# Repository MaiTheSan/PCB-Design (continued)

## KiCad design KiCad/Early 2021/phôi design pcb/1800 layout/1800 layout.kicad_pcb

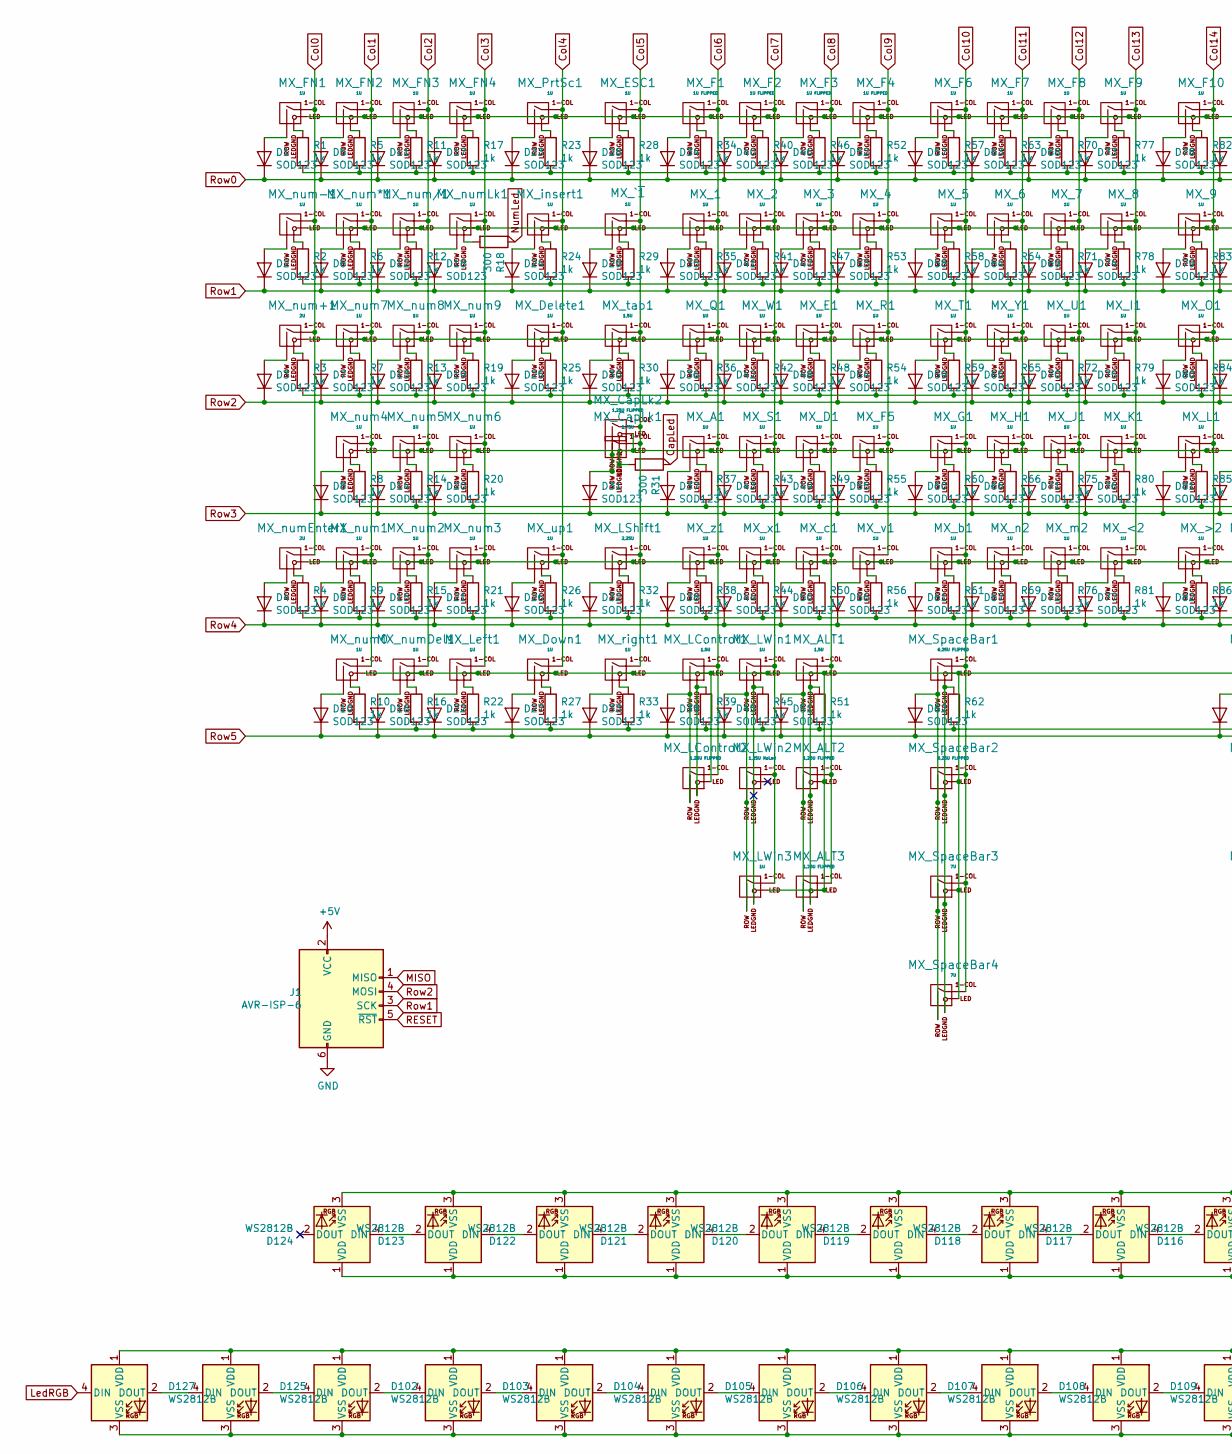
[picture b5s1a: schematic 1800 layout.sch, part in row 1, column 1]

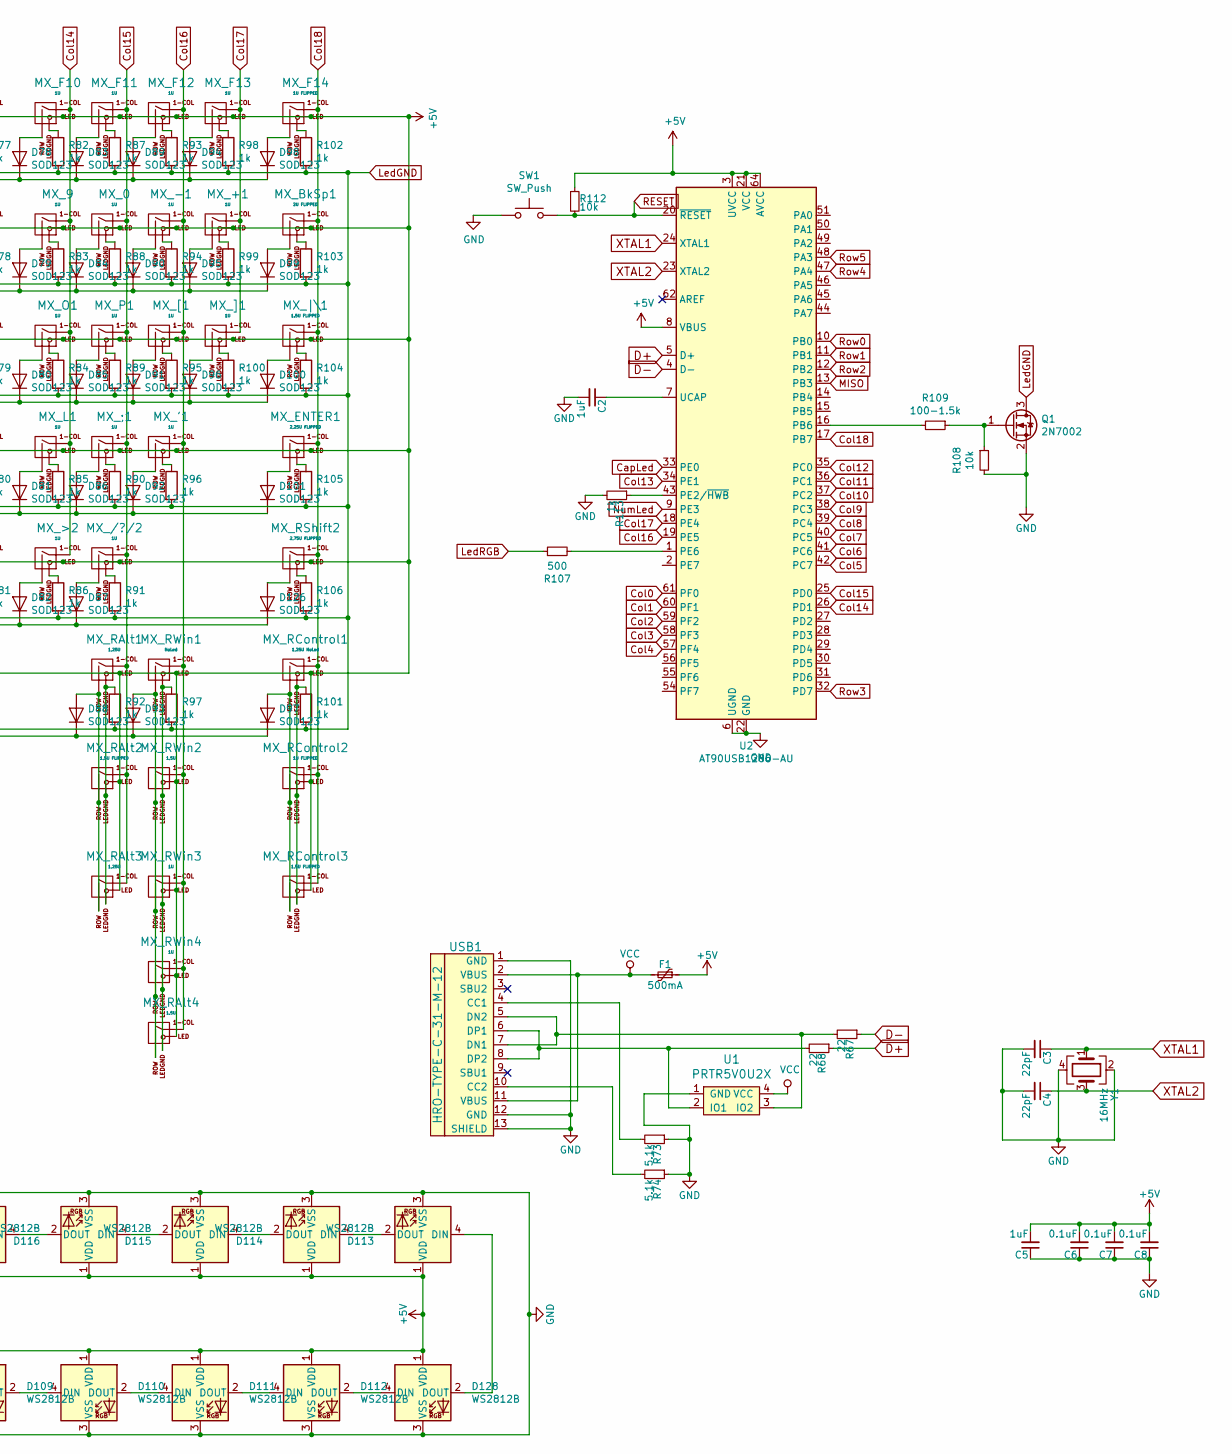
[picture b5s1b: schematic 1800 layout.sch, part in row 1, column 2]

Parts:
C2, C5: 1uF; C_0603
C3, C4: 22pF; C_0603
C6, C7, C8: 0.1uF; C_0603
D1, D2, D3, D4, D5, D6, D7, D8, D9, D10, D11, D12, D13, D14, D15, D16, D17, D18, D19, D20, D21, D22, D23, D24, D25, D26, D27, D28, D29, D30, D31, D32, D33, D34, D35, D36, D37, D38, D39, D40, D41, D42, D43, D44, D45, D46, D47, D48, D49, D50, D51, D52, D53, D54, D55, D56, D57, D58, D59, D60, D61, D62, D63, D64, D65, D66, D67, D68, D69, D70, D71, D72, D73, D74, D75, D76, D77, D78, D79, D80, D81, D82, D83, D84, D85, D86, D87, D88, D89, D90, D91, D92, D93, D94, D95, D96, D97, D98, D99, D100, D101, D126: SOD123; D_SOD-123-Pretty
D102, D103, D104, D105, D106, D107, D108, D109, D110, D111, D112, D113, D114, D115, D116, D117, D118, D119, D120, D121, D122, D123, D124, D125, D127, D128: WS2812B; LED_WS2812B_PLCC4_5.0x5.0mm_P3.2mm
F1: 500mA; Fuse_SMD1206_Reflow
J1: AVR-ISP-6; Reset_Pretty-Mask
MX_0, MX_1, MX_2, MX_3, MX_4, MX_5, MX_6, MX_7, MX_8, MX_9: 1U; MXOnly-1U
MX_'1: 1U; MXOnly-1U
MX_+1: 1U; MXOnly-1U
MX_-1: 1U; MXOnly-1U
MX_/?/2: 1U; MXOnly-1U
MX_;1: 1U; MXOnly-1U
MX_<2: 1U; MXOnly-1U
MX_>2: 1U; MXOnly-1U
MX_A1: 1U; MXOnly-1U
MX_ALT1: 1,5U; MXOnly-1.5U
MX_ALT2, MX_ALT3: 1,25U FLIPPED; MXOnly-1.25U-FLIPPED
MX_BkSp1: 2U FLIPPED; MXOnly-2U-FLIPPED
MX_CapLk1: 1,75U; MXOnly-1.75U
MX_CapLk2: 1,25U FLIPPED; MXOnly-1.25U-FLIPPED
MX_D1: 1U; MXOnly-1U
MX_Delete1: 1U; MXOnly-1U
MX_Down1: 1U; MXOnly-1U
MX_E1: 1U; MXOnly-1U
MX_ENTER1: 2,25U FLIPPED; MXOnly-2.25U-FLIPPED-ReversedStabilizers
MX_ESC1: 1U; MXOnly-1U
MX_F1, MX_F2, MX_F3, MX_F4, MX_F14: 1U FLIPPED; MXOnly-1U-FLIPPED
MX_F5, MX_F6, MX_F7, MX_F8, MX_F9, MX_F10, MX_F11, MX_F12, MX_F13: 1U; MXOnly-1U
MX_FN1, MX_FN2, MX_FN3, MX_FN4: 1U; MXOnly-1U
MX_G1: 1U; MXOnly-1U
MX_H1: 1U; MXOnly-1U
MX_I1: 1U; MXOnly-1U
MX_J1: 1U; MXOnly-1U
MX_K1: 1U; MXOnly-1U
MX_L1: 1U; MXOnly-1U
MX_LControl1: 1,5U; MXOnly-1.5U
MX_LControl2: 1,25U FLIPPED; MXOnly-1.25U-FLIPPED
MX_LShift1: 2,25U; MXOnly-2.25U
MX_LWin1, MX_LWin3: 1U; MXOnly-1U
MX_LWin2: 1,25U NoLed; MXOnly-1.25U-NoLED
MX_Left1: 1U; MXOnly-1U
MX_O1: 1U; MXOnly-1U
MX_P1: 1U; MXOnly-1U
MX_PrtSc1: 1U; MXOnly-1U
MX_Q1: 1U; MXOnly-1U
MX_R1: 1U; MXOnly-1U
MX_RAlt1, MX_RAlt3: 1,25U; MXOnly-1.25U
MX_RAlt2: 1,5U FLIPPED; MXOnly-1.5U-FLIPPED
MX_RAlt4: 1,5U; MXOnly-1.5U
MX_RControl1: 1,25U NoLed; MXOnly-1.25U-NoLED
MX_RControl2: 1U FLIPPED; MXOnly-1U-FLIPPED
MX_RControl3: 1,5U FLIPPED; MXOnly-1.5U-FLIPPED
MX_RShift2: 2,75U FLIPPED; MXOnly-2.75U-FLIPPED
MX_RWin1: NoLed; MXOnly-1.25U-NoLED
MX_RWin2: 1,5U; MXOnly-1.5U
MX_RWin3, MX_RWin4: 1U; MXOnly-1U
MX_S1: 1U; MXOnly-1U
MX_SpaceBar1, MX_SpaceBar2: 6,25U FLIPPED; MXOnly-6.25U-FLIPPED-ReversedStabilizers
MX_SpaceBar3, MX_SpaceBar4: 7U; MXOnly-7U-ReversedStabilizers
MX_T1: 1U; MXOnly-1U
MX_U1: 1U; MXOnly-1U
MX_W1: 1U; MXOnly-1U
MX_Y1: 1U; MXOnly-1U
MX_[1: 1U; MXOnly-1U
MX_]1: 1U; MXOnly-1U
MX_`~1: 1U; MXOnly-1U
MX_b1: 1U; MXOnly-1U
MX_c1: 1U; MXOnly-1U
MX_insert1: 1U; MXOnly-1U
MX_m2: 1U; MXOnly-1U
MX_n2: 1U; MXOnly-1U
MX_num0, MX_num1, MX_num2, MX_num3, MX_num4, MX_num5, MX_num6, MX_num7, MX_num8, MX_num9: 1U; MXOnly-1U
MX_num*1: 1U; MXOnly-1U
MX_num+1: 2U; MXOnly-2U
MX_num-1: 1U; MXOnly-1U
MX_num/1: 1U; MXOnly-1U
MX_numDel1: 1U; MXOnly-1U
MX_numEnter1: 2U; MXOnly-2U
MX_numLk1: 1U; MXOnly-1U
MX_right1: 1U; MXOnly-1U
MX_tab1: 1,5U; MXOnly-1.5U
MX_up1: 1U; MXOnly-1U
MX_v1: 1U; MXOnly-1U
MX_x1: 1U; MXOnly-1U
MX_z1: 1U; MXOnly-1U
MX_|\1: 1.5U FLIPPED; MXOnly-1.5U-FLIPPED
Q1: 2N7002; SOT-23
R1, R2, R3, R4, R5, R6, R7, R8, R9, R10, R11, R12, R13, R14, R15, R16, R17, R19, R20, R21, R22, R23, R24, R25, R26, R27, R28, R29, R30, R32, R33, R34, R35, R36, R37, R38, R39, R40, R41, R42, R43, R44, R45, R46, R47, R48, R49, R50, R51, R52, R53, R54, R55, R56, R57, R58, R59, R60, R61, R62, R63, R64, R65, R66, R69, R70, R71, R72, R75, R76, R77, R78, R79, R80, R81, R82, R83, R84, R85, R86, R87, R88, R89, R90, R91, R92, R93, R94, R95, R96, R97, R98, R99, R100, R101, R102, R103, R104, R105, R106, R113: 1k; R_0805
R18, R31: 300; R_0805
R67, R68: 22; R_0805
R73, R74: 5.1k; R_0805
R107: 500; R_0805
R108, R112: 10k; R_0805
R109: 100-1.5k; R_0805
SW1: SW_Push; SKQG-1155865
U1: PRTR5V0U2X; SOT143B
U2: AT90USB1286-AU; TQFP-64_14x14mm_P0.8mm
USB1: HRO-TYPE-C-31-M-12; HRO-TYPE-C-31-M-12-Assembly
Y1: 16MHz; Crystal_SMD_3225-4Pin_3.2x2.5mm

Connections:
+5V: C5.2, C6.2, C7.2, C8.2, D102.1 (VDD), D103.1 (VDD), D104.1 (VDD), D105.1 (VDD), D106.1 (VDD), D107.1 (VDD), D108.1 (VDD), D109.1 (VDD), D110.1 (VDD), D111.1 (VDD), D112.1 (VDD), D113.1 (VDD), D114.1 (VDD), D115.1 (VDD), D116.1 (VDD), D117.1 (VDD), D118.1 (VDD), D119.1 (VDD), D120.1 (VDD), D121.1 (VDD), D122.1 (VDD), D123.1 (VDD), D124.1 (VDD), D125.1 (VDD), D127.1 (VDD), D128.1 (VDD), F1.1, J1.2 (VCC), MX_0.3 (LED), MX_1.3 (LED), MX_2.3 (LED), MX_3.3 (LED), MX_4.3 (LED), MX_5.3 (LED), MX_6.3 (LED), MX_7.3 (LED), MX_8.3 (LED), MX_9.3 (LED), MX_'1.3 (LED), MX_+1.3 (LED), MX_-1.3 (LED), MX_/?/2.3 (LED), MX_;1.3 (LED), MX_<2.3 (LED), MX_>2.3 (LED), MX_A1.3 (LED), MX_ALT1.3 (LED), MX_ALT2.3 (LED), MX_ALT3.3 (LED), MX_BkSp1.3 (LED), MX_CapLk1.3 (LED), MX_CapLk2.3 (LED), MX_D1.3 (LED), MX_Delete1.3 (LED), MX_Down1.3 (LED), MX_E1.3 (LED), MX_ENTER1.3 (LED), MX_ESC1.3 (LED), MX_F1.3 (LED), MX_F2.3 (LED), MX_F3.3 (LED), MX_F4.3 (LED), MX_F5.3 (LED), MX_F6.3 (LED), MX_F7.3 (LED), MX_F8.3 (LED), MX_F9.3 (LED), MX_F10.3 (LED), MX_F11.3 (LED), MX_F12.3 (LED), MX_F13.3 (LED), MX_F14.3 (LED), MX_FN1.3 (LED), MX_FN2.3 (LED), MX_FN3.3 (LED), MX_FN4.3 (LED), MX_G1.3 (LED), MX_H1.3 (LED), MX_I1.3 (LED), MX_J1.3 (LED), MX_K1.3 (LED), MX_L1.3 (LED), MX_LControl1.3 (LED), MX_LControl2.3 (LED), MX_LShift1.3 (LED), MX_LWin1.3 (LED), MX_LWin3.3 (LED), MX_Left1.3 (LED), MX_O1.3 (LED), MX_P1.3 (LED), MX_PrtSc1.3 (LED), MX_Q1.3 (LED), MX_R1.3 (LED), MX_RAlt1.3 (LED), MX_RAlt2.3 (LED), MX_RAlt3.3 (LED), MX_RAlt4.3 (LED), MX_RControl1.3 (LED), MX_RControl2.3 (LED), MX_RControl3.3 (LED), MX_RShift2.3 (LED), MX_RWin1.3 (LED), MX_RWin2.3 (LED), MX_RWin3.3 (LED), MX_RWin4.3 (LED), MX_S1.3 (LED), MX_SpaceBar1.3 (LED), MX_SpaceBar2.3 (LED), MX_SpaceBar3.3 (LED), MX_SpaceBar4.3 (LED), MX_T1.3 (LED), MX_U1.3 (LED), MX_W1.3 (LED), MX_Y1.3 (LED), MX_[1.3 (LED), MX_]1.3 (LED), MX_`~1.3 (LED), MX_b1.3 (LED), MX_c1.3 (LED), MX_insert1.3 (LED), MX_m2.3 (LED), MX_n2.3 (LED), MX_num0.3 (LED), MX_num1.3 (LED), MX_num2.3 (LED), MX_num3.3 (LED), MX_num4.3 (LED), MX_num5.3 (LED), MX_num6.3 (LED), MX_num7.3 (LED), MX_num8.3 (LED), MX_num9.3 (LED), MX_num*1.3 (LED), MX_num+1.3 (LED), MX_num-1.3 (LED), MX_num/1.3 (LED), MX_numDel1.3 (LED), MX_numEnter1.3 (LED), MX_numLk1.3 (LED), MX_right1.3 (LED), MX_tab1.3 (LED), MX_up1.3 (LED), MX_v1.3 (LED), MX_x1.3 (LED), MX_z1.3 (LED), MX_|\1.3 (LED), R112.1, U2.3 (UVCC), U2.8 (VBUS), U2.21 (VCC), U2.52 (VCC), U2.64 (AVCC)
CapLed: R31.1, U2.33 (PE0)
Col0: MX_FN1.1 (COL), MX_num+1.1 (COL), MX_num-1.1 (COL), MX_numEnter1.1 (COL), U2.61 (PF0)
Col1: MX_FN2.1 (COL), MX_num0.1 (COL), MX_num1.1 (COL), MX_num4.1 (COL), MX_num7.1 (COL), MX_num*1.1 (COL), U2.60 (PF1)
Col2: MX_FN3.1 (COL), MX_num2.1 (COL), MX_num5.1 (COL), MX_num8.1 (COL), MX_num/1.1 (COL), MX_numDel1.1 (COL), U2.59 (PF2)
Col3: MX_FN4.1 (COL), MX_Left1.1 (COL), MX_num3.1 (COL), MX_num6.1 (COL), MX_num9.1 (COL), MX_numLk1.1 (COL), U2.58 (PF3)
Col4: MX_Delete1.1 (COL), MX_Down1.1 (COL), MX_PrtSc1.1 (COL), MX_insert1.1 (COL), MX_up1.1 (COL), U2.57 (PF4)
Col5: MX_CapLk1.1 (COL), MX_CapLk2.1 (COL), MX_ESC1.1 (COL), MX_LShift1.1 (COL), MX_`~1.1 (COL), MX_right1.1 (COL), MX_tab1.1 (COL), U2.42 (PC7)
Col6: MX_1.1 (COL), MX_A1.1 (COL), MX_F1.1 (COL), MX_LControl1.1 (COL), MX_LControl2.1 (COL), MX_Q1.1 (COL), MX_z1.1 (COL), U2.41 (PC6)
Col7: MX_2.1 (COL), MX_F2.1 (COL), MX_LWin1.1 (COL), MX_LWin2.1 (COL), MX_LWin3.1 (COL), MX_S1.1 (COL), MX_W1.1 (COL), MX_x1.1 (COL), U2.40 (PC5)
Col8: MX_3.1 (COL), MX_ALT1.1 (COL), MX_ALT2.1 (COL), MX_ALT3.1 (COL), MX_D1.1 (COL), MX_E1.1 (COL), MX_F3.1 (COL), MX_c1.1 (COL), U2.39 (PC4)
Col9: MX_4.1 (COL), MX_F4.1 (COL), MX_F5.1 (COL), MX_R1.1 (COL), MX_v1.1 (COL), U2.38 (PC3)
Col10: MX_5.1 (COL), MX_F6.1 (COL), MX_G1.1 (COL), MX_SpaceBar1.1 (COL), MX_SpaceBar2.1 (COL), MX_SpaceBar3.1 (COL), MX_SpaceBar4.1 (COL), MX_T1.1 (COL), MX_b1.1 (COL), U2.37 (PC2)
Col11: MX_6.1 (COL), MX_F7.1 (COL), MX_H1.1 (COL), MX_Y1.1 (COL), MX_n2.1 (COL), U2.36 (PC1)
Col12: MX_7.1 (COL), MX_F8.1 (COL), MX_J1.1 (COL), MX_U1.1 (COL), MX_m2.1 (COL), U2.35 (PC0)
Col13: MX_8.1 (COL), MX_<2.1 (COL), MX_F9.1 (COL), MX_I1.1 (COL), MX_K1.1 (COL), U2.34 (PE1)
Col14: MX_9.1 (COL), MX_>2.1 (COL), MX_F10.1 (COL), MX_L1.1 (COL), MX_O1.1 (COL), U2.26 (PD1)
Col15: MX_0.1 (COL), MX_/?/2.1 (COL), MX_;1.1 (COL), MX_F11.1 (COL), MX_P1.1 (COL), MX_RAlt1.1 (COL), MX_RAlt2.1 (COL), MX_RAlt3.1 (COL), U2.25 (PD0)
Col16: MX_'1.1 (COL), MX_-1.1 (COL), MX_F12.1 (COL), MX_RAlt4.1 (COL), MX_RWin1.1 (COL), MX_RWin2.1 (COL), MX_RWin3.1 (COL), MX_RWin4.1 (COL), MX_[1.1 (COL), U2.19 (PE5)
Col17: MX_+1.1 (COL), MX_F13.1 (COL), MX_]1.1 (COL), U2.18 (PE4)
Col18: MX_BkSp1.1 (COL), MX_ENTER1.1 (COL), MX_F14.1 (COL), MX_RControl1.1 (COL), MX_RControl2.1 (COL), MX_RControl3.1 (COL), MX_RShift2.1 (COL), MX_|\1.1 (COL), U2.17 (PB7)
D+: R68.1, U2.5 (D+)
D-: R67.1, U2.4 (D-)
GND: C2.2, C3.2, C4.2, C5.1, C6.1, C7.1, C8.1, D102.3 (VSS), D103.3 (VSS), D104.3 (VSS), D105.3 (VSS), D106.3 (VSS), D107.3 (VSS), D108.3 (VSS), D109.3 (VSS), D110.3 (VSS), D111.3 (VSS), D112.3 (VSS), D113.3 (VSS), D114.3 (VSS), D115.3 (VSS), D116.3 (VSS), D117.3 (VSS), D118.3 (VSS), D119.3 (VSS), D120.3 (VSS), D121.3 (VSS), D122.3 (VSS), D123.3 (VSS), D124.3 (VSS), D125.3 (VSS), D127.3 (VSS), D128.3 (VSS), J1.6 (GND), Q1.2 (S), R73.1, R74.1, R108.2, R113.2, SW1.1, U1.1 (GND), U2.6 (UGND), U2.22 (GND), U2.53 (GND), U2.63 (GND), USB1.1 (GND), USB1.12 (GND), USB1.13 (SHIELD), Y1.2, Y1.4
LedGND: Q1.3 (D), R1.2, R2.2, R3.2, R4.2, R5.2, R6.2, R7.2, R8.2, R9.2, R10.2, R11.2, R12.2, R13.2, R14.2, R15.2, R16.2, R17.2, R19.2, R20.2, R21.2, R22.2, R23.2, R24.2, R25.2, R26.2, R27.2, R28.2, R29.2, R30.2, R32.2, R33.2, R34.2, R35.2, R36.2, R37.2, R38.2, R39.2, R40.2, R41.2, R42.2, R43.2, R44.2, R45.2, R46.2, R47.2, R48.2, R49.2, R50.2, R51.2, R52.2, R53.2, R54.2, R55.2, R56.2, R57.2, R58.2, R59.2, R60.2, R61.2, R62.2, R63.2, R64.2, R65.2, R66.2, R69.2, R70.2, R71.2, R72.2, R75.2, R76.2, R77.2, R78.2, R79.2, R80.2, R81.2, R82.2, R83.2, R84.2, R85.2, R86.2, R87.2, R88.2, R89.2, R90.2, R91.2, R92.2, R93.2, R94.2, R95.2, R96.2, R97.2, R98.2, R99.2, R100.2, R101.2, R102.2, R103.2, R104.2, R105.2, R106.2
LedRGB: D127.4 (DIN), R107.1
MISO: J1.1 (MISO), U2.13 (PB3)
unnamed: C2.1, U2.7 (UCAP)
unnamed: D1.2 (A), MX_FN1.2 (ROW)
unnamed: D2.2 (A), MX_num-1.2 (ROW)
unnamed: D3.2 (A), MX_num+1.2 (ROW)
unnamed: D4.2 (A), MX_numEnter1.2 (ROW)
unnamed: D5.2 (A), MX_FN2.2 (ROW)
unnamed: D6.2 (A), MX_num*1.2 (ROW)
unnamed: D7.2 (A), MX_num7.2 (ROW)
unnamed: D8.2 (A), MX_num4.2 (ROW)
unnamed: D9.2 (A), MX_num1.2 (ROW)
unnamed: D10.2 (A), MX_num0.2 (ROW)
unnamed: D11.2 (A), MX_FN3.2 (ROW)
unnamed: D12.2 (A), MX_num/1.2 (ROW)
unnamed: D13.2 (A), MX_num8.2 (ROW)
unnamed: D14.2 (A), MX_num5.2 (ROW)
unnamed: D15.2 (A), MX_num2.2 (ROW)
unnamed: D16.2 (A), MX_numDel1.2 (ROW)
unnamed: D17.2 (A), MX_FN4.2 (ROW)
unnamed: D18.2 (A), MX_numLk1.2 (ROW)
unnamed: D19.2 (A), MX_num9.2 (ROW)
unnamed: D20.2 (A), MX_num6.2 (ROW)
unnamed: D21.2 (A), MX_num3.2 (ROW)
unnamed: D22.2 (A), MX_Left1.2 (ROW)
unnamed: D23.2 (A), MX_PrtSc1.2 (ROW)
unnamed: D24.2 (A), MX_insert1.2 (ROW)
unnamed: D25.2 (A), MX_Delete1.2 (ROW)
unnamed: D26.2 (A), MX_up1.2 (ROW)
unnamed: D27.2 (A), MX_Down1.2 (ROW)
unnamed: D28.2 (A), MX_ESC1.2 (ROW)
unnamed: D29.2 (A), MX_`~1.2 (ROW)
unnamed: D30.2 (A), MX_tab1.2 (ROW)
unnamed: D31.2 (A), MX_CapLk1.2 (ROW), MX_CapLk2.2 (ROW)
unnamed: D32.2 (A), MX_LShift1.2 (ROW)
unnamed: D33.2 (A), MX_right1.2 (ROW)
unnamed: D34.2 (A), MX_F1.2 (ROW)
unnamed: D35.2 (A), MX_1.2 (ROW)
unnamed: D36.2 (A), MX_Q1.2 (ROW)
unnamed: D37.2 (A), MX_A1.2 (ROW)
unnamed: D38.2 (A), MX_z1.2 (ROW)
unnamed: D39.2 (A), MX_LControl1.2 (ROW), MX_LControl2.2 (ROW)
unnamed: D40.2 (A), MX_F2.2 (ROW)
unnamed: D41.2 (A), MX_2.2 (ROW)
unnamed: D42.2 (A), MX_W1.2 (ROW)
unnamed: D43.2 (A), MX_S1.2 (ROW)
unnamed: D44.2 (A), MX_x1.2 (ROW)
unnamed: D45.2 (A), MX_LWin1.2 (ROW), MX_LWin2.2 (ROW), MX_LWin3.2 (ROW)
unnamed: D46.2 (A), MX_F3.2 (ROW)
unnamed: D47.2 (A), MX_3.2 (ROW)
unnamed: D48.2 (A), MX_E1.2 (ROW)
unnamed: D49.2 (A), MX_D1.2 (ROW)
unnamed: D50.2 (A), MX_c1.2 (ROW)
unnamed: D51.2 (A), MX_ALT1.2 (ROW), MX_ALT2.2 (ROW), MX_ALT3.2 (ROW)
unnamed: D52.2 (A), MX_F4.2 (ROW)
unnamed: D53.2 (A), MX_4.2 (ROW)
unnamed: D54.2 (A), MX_R1.2 (ROW)
unnamed: D55.2 (A), MX_F5.2 (ROW)
unnamed: D56.2 (A), MX_v1.2 (ROW)
unnamed: D57.2 (A), MX_F6.2 (ROW)
unnamed: D58.2 (A), MX_5.2 (ROW)
unnamed: D59.2 (A), MX_T1.2 (ROW)
unnamed: D60.2 (A), MX_G1.2 (ROW)
unnamed: D61.2 (A), MX_b1.2 (ROW)
unnamed: D62.2 (A), MX_SpaceBar1.2 (ROW), MX_SpaceBar2.2 (ROW), MX_SpaceBar3.2 (ROW), MX_SpaceBar4.2 (ROW)
unnamed: D63.2 (A), MX_F7.2 (ROW)
unnamed: D64.2 (A), MX_6.2 (ROW)
unnamed: D65.2 (A), MX_Y1.2 (ROW)
unnamed: D66.2 (A), MX_H1.2 (ROW)
unnamed: D67.2 (A), MX_n2.2 (ROW)
unnamed: D68.2 (A), MX_F8.2 (ROW)
unnamed: D69.2 (A), MX_7.2 (ROW)
unnamed: D70.2 (A), MX_U1.2 (ROW)
unnamed: D71.2 (A), MX_J1.2 (ROW)
unnamed: D72.2 (A), MX_m2.2 (ROW)
unnamed: D73.2 (A), MX_F9.2 (ROW)
unnamed: D74.2 (A), MX_8.2 (ROW)
unnamed: D75.2 (A), MX_I1.2 (ROW)
unnamed: D76.2 (A), MX_K1.2 (ROW)
unnamed: D77.2 (A), MX_<2.2 (ROW)
unnamed: D78.2 (A), MX_F10.2 (ROW)
unnamed: D79.2 (A), MX_9.2 (ROW)
unnamed: D80.2 (A), MX_O1.2 (ROW)
unnamed: D81.2 (A), MX_L1.2 (ROW)
unnamed: D82.2 (A), MX_>2.2 (ROW)
unnamed: D83.2 (A), MX_F11.2 (ROW)
unnamed: D84.2 (A), MX_0.2 (ROW)
unnamed: D85.2 (A), MX_P1.2 (ROW)
unnamed: D86.2 (A), MX_;1.2 (ROW)
unnamed: D87.2 (A), MX_/?/2.2 (ROW)
unnamed: D88.2 (A), MX_RAlt1.2 (ROW), MX_RAlt2.2 (ROW), MX_RAlt3.2 (ROW)
unnamed: D89.2 (A), MX_F12.2 (ROW)
unnamed: D90.2 (A), MX_-1.2 (ROW)
unnamed: D91.2 (A), MX_[1.2 (ROW)
unnamed: D92.2 (A), MX_'1.2 (ROW)
unnamed: D93.2 (A), MX_RAlt4.2 (ROW), MX_RWin1.2 (ROW), MX_RWin2.2 (ROW), MX_RWin3.2 (ROW), MX_RWin4.2 (ROW)
unnamed: D94.2 (A), MX_F13.2 (ROW)
unnamed: D95.2 (A), MX_+1.2 (ROW)
unnamed: D96.2 (A), MX_]1.2 (ROW)
unnamed: D97.2 (A), MX_RControl1.2 (ROW), MX_RControl2.2 (ROW), MX_RControl3.2 (ROW)
unnamed: D98.2 (A), MX_F14.2 (ROW)
unnamed: D99.2 (A), MX_BkSp1.2 (ROW)
unnamed: D100.2 (A), MX_|\1.2 (ROW)
unnamed: D101.2 (A), MX_ENTER1.2 (ROW)
unnamed: D102.2 (DOUT), D103.4 (DIN)
unnamed: D102.4 (DIN), D125.2 (DOUT)
unnamed: D103.2 (DOUT), D104.4 (DIN)
unnamed: D104.2 (DOUT), D105.4 (DIN)
unnamed: D105.2 (DOUT), D106.4 (DIN)
unnamed: D106.2 (DOUT), D107.4 (DIN)
unnamed: D107.2 (DOUT), D108.4 (DIN)
unnamed: D108.2 (DOUT), D109.4 (DIN)
unnamed: D109.2 (DOUT), D110.4 (DIN)
unnamed: D110.2 (DOUT), D111.4 (DIN)
unnamed: D111.2 (DOUT), D112.4 (DIN)
unnamed: D112.2 (DOUT), D128.4 (DIN)
unnamed: D113.2 (DOUT), D114.4 (DIN)
unnamed: D113.4 (DIN), D128.2 (DOUT)
unnamed: D114.2 (DOUT), D115.4 (DIN)
unnamed: D115.2 (DOUT), D116.4 (DIN)
unnamed: D116.2 (DOUT), D117.4 (DIN)
unnamed: D117.2 (DOUT), D118.4 (DIN)
unnamed: D118.2 (DOUT), D119.4 (DIN)
unnamed: D119.2 (DOUT), D120.4 (DIN)
unnamed: D120.2 (DOUT), D121.4 (DIN)
unnamed: D121.2 (DOUT), D122.4 (DIN)
unnamed: D122.2 (DOUT), D123.4 (DIN)
unnamed: D123.2 (DOUT), D124.4 (DIN)
unnamed: D125.4 (DIN), D127.2 (DOUT)
unnamed: D126.2 (A), MX_RShift2.2 (ROW)
unnamed: MX_0.4 (LEDGND), R88.1
unnamed: MX_1.4 (LEDGND), R35.1
unnamed: MX_2.4 (LEDGND), R41.1
unnamed: MX_3.4 (LEDGND), R47.1
unnamed: MX_4.4 (LEDGND), R53.1
unnamed: MX_5.4 (LEDGND), R58.1
unnamed: MX_6.4 (LEDGND), R64.1
unnamed: MX_7.4 (LEDGND), R71.1
unnamed: MX_8.4 (LEDGND), R78.1
unnamed: MX_9.4 (LEDGND), R83.1
unnamed: MX_'1.4 (LEDGND), R96.1
unnamed: MX_+1.4 (LEDGND), R99.1
unnamed: MX_-1.4 (LEDGND), R94.1
unnamed: MX_/?/2.4 (LEDGND), R91.1
unnamed: MX_;1.4 (LEDGND), R90.1
unnamed: MX_<2.4 (LEDGND), R81.1
unnamed: MX_>2.4 (LEDGND), R86.1
unnamed: MX_A1.4 (LEDGND), R37.1
unnamed: MX_ALT1.4 (LEDGND), MX_ALT2.4 (LEDGND), MX_ALT3.4 (LEDGND), R51.1
unnamed: MX_BkSp1.4 (LEDGND), R103.1
unnamed: MX_CapLk1.4 (LEDGND), MX_CapLk2.4 (LEDGND), R31.2
unnamed: MX_D1.4 (LEDGND), R49.1
unnamed: MX_Delete1.4 (LEDGND), R25.1
unnamed: MX_Down1.4 (LEDGND), R27.1
unnamed: MX_E1.4 (LEDGND), R48.1
unnamed: MX_ENTER1.4 (LEDGND), R105.1
unnamed: MX_ESC1.4 (LEDGND), R28.1
unnamed: MX_F1.4 (LEDGND), R34.1
unnamed: MX_F2.4 (LEDGND), R40.1
unnamed: MX_F3.4 (LEDGND), R46.1
unnamed: MX_F4.4 (LEDGND), R52.1
unnamed: MX_F5.4 (LEDGND), R55.1
unnamed: MX_F6.4 (LEDGND), R57.1
unnamed: MX_F7.4 (LEDGND), R63.1
unnamed: MX_F8.4 (LEDGND), R70.1
unnamed: MX_F9.4 (LEDGND), R77.1
unnamed: MX_F10.4 (LEDGND), R82.1
unnamed: MX_F11.4 (LEDGND), R87.1
unnamed: MX_F12.4 (LEDGND), R93.1
unnamed: MX_F13.4 (LEDGND), R98.1
unnamed: MX_F14.4 (LEDGND), R102.1
unnamed: MX_FN1.4 (LEDGND), R1.1
unnamed: MX_FN2.4 (LEDGND), R5.1
unnamed: MX_FN3.4 (LEDGND), R11.1
unnamed: MX_FN4.4 (LEDGND), R17.1
unnamed: MX_G1.4 (LEDGND), R60.1
unnamed: MX_H1.4 (LEDGND), R66.1
unnamed: MX_I1.4 (LEDGND), R79.1
unnamed: MX_J1.4 (LEDGND), R75.1
unnamed: MX_K1.4 (LEDGND), R80.1
unnamed: MX_L1.4 (LEDGND), R85.1
unnamed: MX_LControl1.4 (LEDGND), MX_LControl2.4 (LEDGND), R39.1
unnamed: MX_LShift1.4 (LEDGND), R32.1
unnamed: MX_LWin1.4 (LEDGND), MX_LWin3.4 (LEDGND), R45.1
unnamed: MX_Left1.4 (LEDGND), R22.1
unnamed: MX_O1.4 (LEDGND), R84.1
unnamed: MX_P1.4 (LEDGND), R89.1
unnamed: MX_PrtSc1.4 (LEDGND), R23.1
unnamed: MX_Q1.4 (LEDGND), R36.1
unnamed: MX_R1.4 (LEDGND), R54.1
unnamed: MX_RAlt1.4 (LEDGND), MX_RAlt2.4 (LEDGND), MX_RAlt3.4 (LEDGND), R92.1
unnamed: MX_RAlt4.4 (LEDGND), MX_RWin1.4 (LEDGND), MX_RWin2.4 (LEDGND), MX_RWin3.4 (LEDGND), MX_RWin4.4 (LEDGND), R97.1
unnamed: MX_RControl1.4 (LEDGND), MX_RControl2.4 (LEDGND), MX_RControl3.4 (LEDGND), R101.1
unnamed: MX_RShift2.4 (LEDGND), R106.1
unnamed: MX_S1.4 (LEDGND), R43.1
unnamed: MX_SpaceBar1.4 (LEDGND), MX_SpaceBar2.4 (LEDGND), MX_SpaceBar3.4 (LEDGND), MX_SpaceBar4.4 (LEDGND), R62.1
unnamed: MX_T1.4 (LEDGND), R59.1
unnamed: MX_U1.4 (LEDGND), R72.1
unnamed: MX_W1.4 (LEDGND), R42.1
unnamed: MX_Y1.4 (LEDGND), R65.1
unnamed: MX_[1.4 (LEDGND), R95.1
unnamed: MX_]1.4 (LEDGND), R100.1
unnamed: MX_`~1.4 (LEDGND), R29.1
unnamed: MX_b1.4 (LEDGND), R61.1
unnamed: MX_c1.4 (LEDGND), R50.1
unnamed: MX_insert1.4 (LEDGND), R24.1
unnamed: MX_m2.4 (LEDGND), R76.1
unnamed: MX_n2.4 (LEDGND), R69.1
unnamed: MX_num0.4 (LEDGND), R10.1
unnamed: MX_num1.4 (LEDGND), R9.1
unnamed: MX_num2.4 (LEDGND), R15.1
unnamed: MX_num3.4 (LEDGND), R21.1
unnamed: MX_num4.4 (LEDGND), R8.1
unnamed: MX_num5.4 (LEDGND), R14.1
unnamed: MX_num6.4 (LEDGND), R20.1
unnamed: MX_num7.4 (LEDGND), R7.1
unnamed: MX_num8.4 (LEDGND), R13.1
unnamed: MX_num9.4 (LEDGND), R19.1
unnamed: MX_num*1.4 (LEDGND), R6.1
unnamed: MX_num+1.4 (LEDGND), R3.1
unnamed: MX_num-1.4 (LEDGND), R2.1
unnamed: MX_num/1.4 (LEDGND), R12.1
unnamed: MX_numDel1.4 (LEDGND), R16.1
unnamed: MX_numEnter1.4 (LEDGND), R4.1
unnamed: MX_numLk1.4 (LEDGND), R18.2
unnamed: MX_right1.4 (LEDGND), R33.1
unnamed: MX_tab1.4 (LEDGND), R30.1
unnamed: MX_up1.4 (LEDGND), R26.1
unnamed: MX_v1.4 (LEDGND), R56.1
unnamed: MX_x1.4 (LEDGND), R44.1
unnamed: MX_z1.4 (LEDGND), R38.1
unnamed: MX_|\1.4 (LEDGND), R104.1
unnamed: Q1.1 (G), R108.1, R109.1
unnamed: R67.2, U1.3 (IO2), USB1.5 (DN2), USB1.7 (DN1)
unnamed: R68.2, U1.2 (IO1), USB1.6 (DP1), USB1.8 (DP2)
unnamed: R73.2, USB1.4 (CC1)
unnamed: R74.2, USB1.10 (CC2)
unnamed: R107.2, U2.1 (PE6)
unnamed: R109.2, U2.16 (PB6)
unnamed: R113.1, U2.43 (PE2/~HWB)
NumLed: R18.1, U2.9 (PE3)
RESET: J1.5 (~RST), R112.2, SW1.2, U2.20 (~RESET)
Row0: D1.1 (K), D5.1 (K), D11.1 (K), D17.1 (K), D23.1 (K), D28.1 (K), D34.1 (K), D40.1 (K), D46.1 (K), D52.1 (K), D57.1 (K), D63.1 (K), D68.1 (K), D73.1 (K), D78.1 (K), D83.1 (K), D89.1 (K), D94.1 (K), D98.1 (K), U2.10 (PB0)
Row1: D2.1 (K), D6.1 (K), D12.1 (K), D18.1 (K), D24.1 (K), D29.1 (K), D35.1 (K), D41.1 (K), D47.1 (K), D53.1 (K), D58.1 (K), D64.1 (K), D69.1 (K), D74.1 (K), D79.1 (K), D84.1 (K), D90.1 (K), D95.1 (K), D99.1 (K), J1.3 (SCK), U2.11 (PB1)
Row2: D3.1 (K), D7.1 (K), D13.1 (K), D19.1 (K), D25.1 (K), D30.1 (K), D36.1 (K), D42.1 (K), D48.1 (K), D54.1 (K), D59.1 (K), D65.1 (K), D70.1 (K), D75.1 (K), D80.1 (K), D85.1 (K), D91.1 (K), D96.1 (K), D100.1 (K), J1.4 (MOSI), U2.12 (PB2)
Row3: D8.1 (K), D14.1 (K), D20.1 (K), D31.1 (K), D37.1 (K), D43.1 (K), D49.1 (K), D55.1 (K), D60.1 (K), D66.1 (K), D71.1 (K), D76.1 (K), D81.1 (K), D86.1 (K), D92.1 (K), D101.1 (K), U2.32 (PD7)
Row4: D4.1 (K), D9.1 (K), D15.1 (K), D21.1 (K), D26.1 (K), D32.1 (K), D38.1 (K), D44.1 (K), D50.1 (K), D56.1 (K), D61.1 (K), D67.1 (K), D72.1 (K), D77.1 (K), D82.1 (K), D87.1 (K), D126.1 (K), U2.47 (PA4)
Row5: D10.1 (K), D16.1 (K), D22.1 (K), D27.1 (K), D33.1 (K), D39.1 (K), D45.1 (K), D51.1 (K), D62.1 (K), D88.1 (K), D93.1 (K), D97.1 (K), U2.48 (PA3)
VCC: F1.2, U1.4 (VCC), USB1.2 (VBUS), USB1.11 (VBUS)
XTAL1: C3.1, U2.24 (XTAL1), Y1.1
XTAL2: C4.1, U2.23 (XTAL2), Y1.3

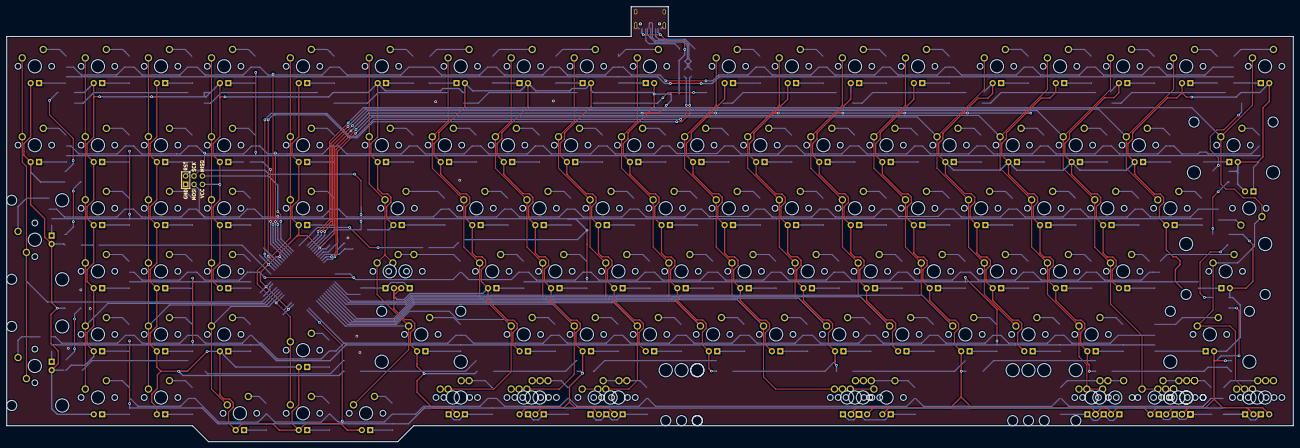
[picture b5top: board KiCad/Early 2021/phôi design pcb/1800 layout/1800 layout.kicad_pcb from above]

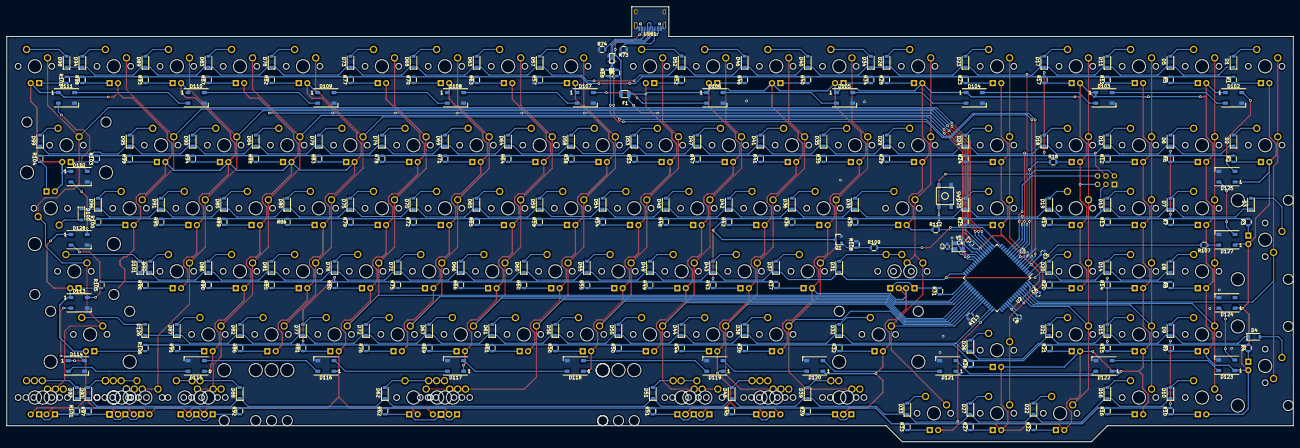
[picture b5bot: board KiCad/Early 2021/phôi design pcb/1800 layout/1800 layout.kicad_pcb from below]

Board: 2 copper layers, 388.5 x 131.3 mm, 373 parts (253 on the bottom side), 276 nets.
